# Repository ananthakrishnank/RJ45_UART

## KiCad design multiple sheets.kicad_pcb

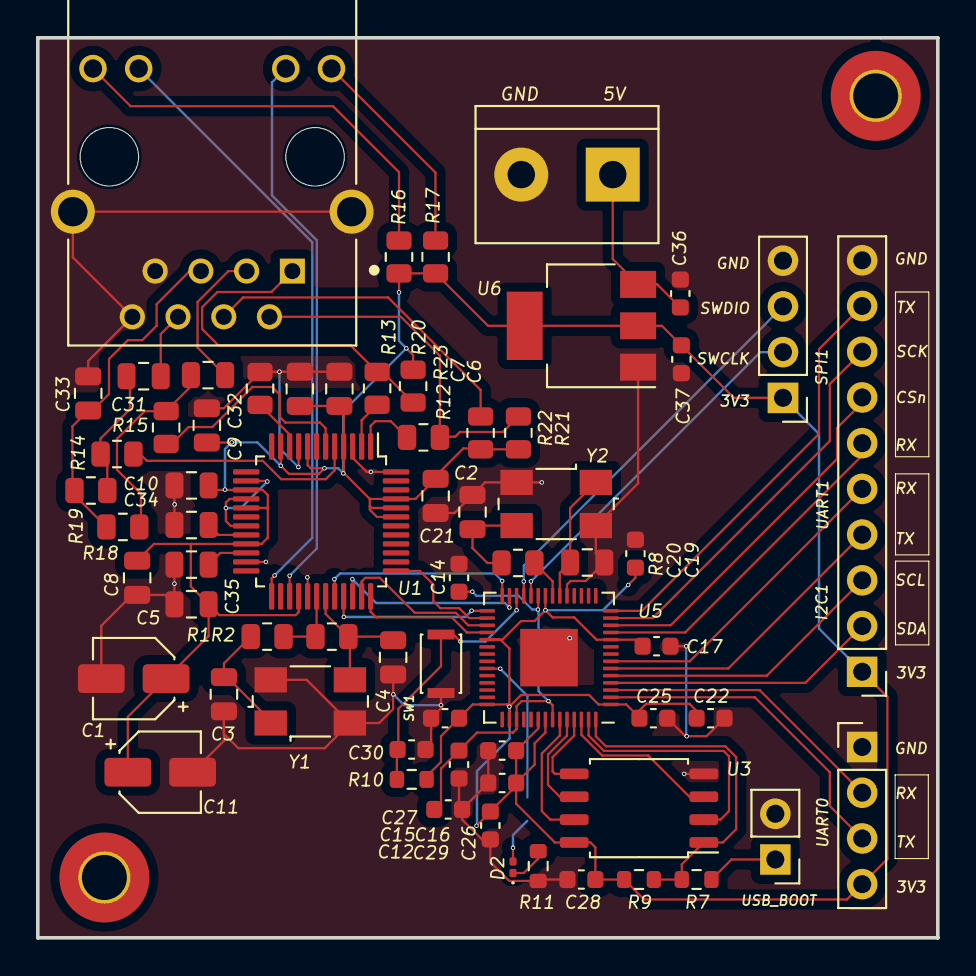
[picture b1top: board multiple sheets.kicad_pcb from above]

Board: 2 copper layers, 50.0 x 50.0 mm, 69 parts (1 on the bottom side), 58 nets.

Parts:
C1, C11: 10uF; CP_Elec_4x3
C2, C5, C6, C7, C8, C9, C10: 100nF; C_0805_2012Metric
C3, C4: 18pF; C_0805_2012Metric
C12, C14, C17, C19, C22, C25, C26, C27, C28, C29: 100n; C_0603_1608Metric
C15: 1U; C_0603_1608Metric
C16, C30: 1u; C_0603_1608Metric
C20, C21: 27pf; C_0805_2012Metric
C31, C32: 6.8nF; C_0805_2012Metric
C33, C35: 10nF; C_0805_2012Metric
C34: 4.7uF; C_0805_2012Metric
C36: 100nF; C_0603_1608Metric
C37: 10uF; C_0603_1608Metric
D2: LED; LED_0201_0603Metric
H1, H2: MountingHole; MountingHole_2.5mm_Pad_TopBottom
J1: Screw_Terminal_01x02; TerminalBlock_bornier-2_P5.08mm
J2: Conn_01x10; PinHeader_1x10_P2.54mm_Vertical
J4: Conn_01x02_Pin; PinHeader_1x02_P2.54mm_Vertical
J6: Conn_01x04; PinHeader_1x04_P2.54mm_Vertical
JP5: SolderJumper_2_Open; SolderJumper-2_P1.3mm_Open_RoundedPad1.0x1.5mm
Jeee1: HR911105A; HANRUN_HR911105A
R1, R12, R13, R14, R15: 0R; R_0805_2012Metric
R2: 1M; R_0805_2012Metric
R7: 1K; R_0603_1608Metric
R8: 1K; R_0805_2012Metric
R9: DNF; R_0603_1608Metric
R10: 10K; R_0603_1608Metric
R11: 470R; R_0603_1608Metric
R16, R17: 330R; R_0805_2012Metric
R18, R19, R20, R21: 49.9R; R_0805_2012Metric
R22: 10.1R; R_0805_2012Metric
R23: 12.4K; R_0805_2012Metric
SW1: BOOT; SW_SPST_CK_KXT3
U1: W5500; LQFP-48_7x7mm_P0.5mm
U3: W25Q128JVS; SOIC-8_5.23x5.23mm_P1.27mm
U5: RP2040; QFN-56-1EP_7x7mm_P0.4mm_EP3.2x3.2mm
U6: LD1117S33TR_SOT223; SOT-223-3_TabPin2
UART0: Conn_01x04; PinHeader_1x04_P2.54mm_Vertical
Y1: Crystal_GND24; Crystal_SMD_0603-4Pin_6.0x3.5mm
Y2: 12MHz; Crystal_SMD_0603-4Pin_6.0x3.5mm

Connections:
+1V1: C12.1, C14.1, C15.1, U5.23 (DVDD), U5.45 (VREG_VOUT), U5.50 (DVDD)
+3V3: C1.1, C2.1, C5.1, C6.1, C7.1, C8.1, C9.1, C10.1, C11.1, C16.1, C17.1, C19.1, C22.1, C25.1, C26.1, C27.1, C28.1, C29.1, C37.1, J2.1, J6.1, R9.1, R10.2, R16.2, R17.2, R20.1, R21.1, R22.1, U1.4 (AVDD), U1.8 (AVDD), U1.11 (AVDD), U1.15 (AVDD), U1.17 (AVDD), U1.21 (AVDD), U1.28 (VDD), U1.43 (PMODE2), U1.44 (PMODE1), U1.45 (PMODE0), U3.8 (VCC), U5.1 (IOVDD), U5.10 (IOVDD), U5.22 (IOVDD), U5.33 (IOVDD), U5.42 (IOVDD), U5.44 (VREG_IN), U5.48 (USB_VDD), U5.49 (IOVDD), U6.2 (VO), UART0.4
/RP2040/GPIO25: JP5.1 (A), U5.37 (GPIO25)
/RP2040/I2C1_SCL: J2.3, U5.5 (GPIO3)
/RP2040/I2C1_SDA: J2.2, U5.4 (GPIO2)
/RP2040/QSPI_SCLK: U3.6 (CLK), U5.52 (QSPI_SCLK)
/RP2040/QSPI_SD0: U3.5 (DI(IO0)), U5.53 (QSPI_SD0)
/RP2040/QSPI_SD1: U3.2 (DO(IO1)), U5.55 (QSPI_SD1)
/RP2040/QSPI_SD2: U3.3 (IO2), U5.54 (QSPI_SD2)
/RP2040/QSPI_SD3: U3.7 (IO3), U5.51 (QSPI_SD3)
/RP2040/QSPI_SS: R7.1, R9.2, U3.1 (~CS), U5.56 (QSPI_SS)
/RP2040/RUN: C30.1, R10.1, SW1.1, U5.26 (RUN)
/RP2040/SPI1_CSn: J2.7, U5.12 (GPIO9)
/RP2040/SPI1_RX: J2.6, U5.11 (GPIO8)
/RP2040/SPI1_SCK: J2.8, U5.13 (GPIO10)
/RP2040/SPI1_TX: J2.9, U5.14 (GPIO11)
/RP2040/SWCLK: J6.2, U5.24 (SWCLK)
/RP2040/SWDIO: J6.3, U5.25 (SWD)
/RP2040/UART0_RX: U5.3 (GPIO1), UART0.2
/RP2040/UART0_TX: U5.2 (GPIO0), UART0.3
/RP2040/UART1_RX: J2.5, U5.7 (GPIO5)
/RP2040/UART1_TX: J2.4, U5.6 (GPIO4)
/RP2040/USB_BOOT: J4.1, R7.2
/RP2040/XIN: C20.2, U5.20 (XIN), Y2.1
/RP2040/XOUT: R8.1, U5.21 (XOUT)
/W5500/INTN: U1.36 (~INT), U5.32 (GPIO21)
/W5500/MISO: U1.34 (MISO), U5.27 (GPIO16)
/W5500/MOSI: U1.35 (MOSI), U5.31 (GPIO20)
/W5500/RSTN: U1.37 (~RST), U5.30 (GPIO19)
/W5500/SCLK: U1.33 (SCLK), U5.29 (GPIO18)
/W5500/SCS: U1.32 (~SCS), U5.28 (GPIO17)
/W5500/XIN: R1.1, R2.1, U1.30 (XI/CLKIN)
/W5500/XOUT: C4.1, R2.2, U1.31 (XO), Y1.3
ACTLED: Jeee1.10, U1.27 (ACTLED)
GND: C1.2, C2.2, C3.2, C4.2, C5.2, C6.2, C7.2, C8.2, C9.2, C10.2, C11.2, C12.2, C14.2, C15.2, C16.2, C17.2, C19.2, C20.1, C21.1, C22.2, C25.2, C26.2, C27.2, C28.2, C29.2, C30.2, C33.2, C34.2, C35.2, C36.2, C37.2, J1.2, J2.10, J4.2, J6.4, Jeee1.7, Jeee1.8, Jeee1.15 (SHIELD), Jeee1.16 (SHIELD), R11.2, R23.1, SW1.2, U1.3 (AGND), U1.9 (AGND), U1.14 (AGND), U1.16 (AGND), U1.19 (AGND), U1.23 (RSVD), U1.29 (GND), U1.48 (AGND), U3.4 (GND), U5.19 (TESTEN), U5.57 (GND), U6.1 (GND), UART0.1, Y1.2, Y1.4, Y2.2, Y2.4
LINKLED: Jeee1.11, U1.25 (LINKLED)
unnamed: C3.1, R1.2, Y1.1
unnamed: C21.2, R8.2, Y2.3
unnamed: C31.1, R14.1, R19.1
unnamed: C31.2, Jeee1.6
unnamed: C32.1, R15.1, R18.1
unnamed: C32.2, Jeee1.3
unnamed: C33.1, Jeee1.5, R18.2, R19.2
unnamed: D2.2 (A), JP5.2 (B)
unnamed: D2.1 (K), R11.1
unnamed: C36.1, J1.1, U6.3 (VI)
unnamed: Jeee1.1, R13.1, R20.2
unnamed: Jeee1.2, R12.1, R21.2
unnamed: Jeee1.4, R22.2
unnamed: Jeee1.9, R17.1
unnamed: Jeee1.12, R16.1
unnamed: C35.1, U1.22 (1V2O)
unnamed: R23.2, U1.10 (EXRES1)
unnamed: R14.2, U1.5 (RXN)
unnamed: R15.2, U1.6 (RXP)
unnamed: C34.1, U1.20 (TOCAP)
unnamed: R12.2, U1.1 (TXN)
unnamed: R13.2, U1.2 (TXP)

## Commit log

2023-06-06 zip file for the RJ45_UART INTERFACING PCB
